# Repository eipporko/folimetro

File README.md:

# Folimetro

Folimetro is able to measure the air pressure into a galician bagpipe, connecting it instead of the ronqueta drone.

## Motivation

One of the most tricky things to do when playing the bagpipe is maintaining the level of the air pressure in the bag, in order to keep the sound of the drones.

The idea behind this project was to give support to the students and teachers of this instrument to control this problem.

## How it works?

This device consist of 9 leds who marks the pressure and 2 push buttons to displace the pressure value of the central led.

```
                                          PRESSURE VALUE (kPA)
          0.2  0.8  1.4  2.0  2.6  3.2  3.8  4.4  5.0  5.6  6.2  6.8  7.4  8.0  8.6  9.2  9.8
                               |    |    |    |    |    |    |    |    |    
                              -4   -3   -2   -1    0    1    2    3    4  
                                            NUMBER OF LED

```

## Project structure
* `docs` - various PDF datasheets for component used.
* `hardware` - Fritzing Schematic.
* `folimetro.ino` - Arduino project.

## Hardware Requirements

* Arduino Micro Pro (Leonardo)
* 11x Leds
* 10x 1k Ohm resistor
* 2x Push button
* 2x 10k Ohm resistor
* Pressure sensor (0 to 10kPA)

## Arduino Schematic

## Reference
1.  Cassandre Balosso-Bardin, Camille Vauthrin, Patricio de la Cuadra, Ilya Franciosi, Khalil Ben Mansour, Lise Ochej. EuroRegio2016 (2016, June 13-15). *\<\<The musical arm of the bagpipe player: a cultural and mechanical approach>>*  [[Link]]( http://www.sea-acustica.es/fileadmin/Oporto16/73.pdf)

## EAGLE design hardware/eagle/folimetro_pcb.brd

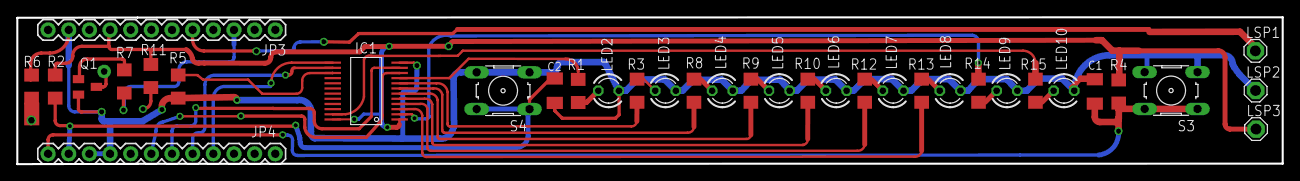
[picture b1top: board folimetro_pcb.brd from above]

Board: 2 copper layers, 155.6 x 18.1 mm, 35 parts (0 on the bottom side), 30 nets.

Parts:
C1, C2: C1206K
IC1: SO24W
JP3, JP4: 1X12
LED2, LED3, LED4, LED5, LED6, LED7, LED8, LED9, LED10: LED3MM
LSP1, LSP2, LSP3: SE13
Q1: BC547; SOT23
R1, R2, R3, R4, R5, R6, R7, R8, R9, R10, R11, R12, R13, R14, R15: R1206
S3, S4: B3F-10XX

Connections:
+5V: IC1.1, IC1.24, JP3.4, LSP3.MP, R2.1, R4.2, R11.2
GND: C1.2, C2.2, IC1.12, JP3.2, JP4.9, JP4.10, LED2.K, LED3.K, LED4.K, LED5.K, LED6.K, LED7.K, LED8.K, LED9.K, LED10.K, LSP2.MP, Q1.2, R5.1, R6.1, S3.3, S3.4, S4.3, S4.4
unnamed: C1.1, JP4.12, R4.1, S3.1, S3.2
unnamed: Q1.1, R7.2
unnamed: IC1.15, R5.2
unnamed: IC1.10, JP4.7
unnamed: IC1.11, JP4.6
unnamed: IC1.14, JP4.5
unnamed: IC1.13, JP4.4
unnamed: IC1.9, R1.2
unnamed: LED2.A, R1.1
unnamed: IC1.8, R3.2
unnamed: LED3.A, R3.1
unnamed: IC1.2, R14.2
unnamed: IC1.7, R8.2
unnamed: LED4.A, R8.1
unnamed: IC1.6, R9.2
unnamed: LED5.A, R9.1
unnamed: IC1.5, R10.2
unnamed: LED6.A, R10.1
unnamed: IC1.4, R12.2
unnamed: LED7.A, R12.1
unnamed: IC1.3, R13.2
unnamed: LED8.A, R13.1
unnamed: IC1.23, R15.2
unnamed: LED9.A, R14.1
unnamed: C2.1, JP4.11, R2.2, S4.1, S4.2
unnamed: LED10.A, R15.1
unnamed: JP3.10, R7.1
unnamed: JP3.8, LSP1.MP

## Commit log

2016-12-15 Added confirmation animation
2016-12-18 Foliometro v1.0
2016-12-18 Rename foliometro.ino to folimetro.ino
2016-12-19 Updated fritzing sketch
2016-12-19 README.md updated
2020-07-04 Adapting the firmware to the pcb developed by my father
2020-07-05 Establishing a delay of 25 ms to send the pressure information throw Bluetooth.
2020-07-30 Removing unused constants
2021-10-15 Changing parameter in the serial
